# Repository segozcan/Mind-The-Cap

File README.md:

# Mind-The-Cap

This is a repository for the hardware project of the [[EE464]] Static Power Conversion II course given by [[METU]] EEE department. 
The aim of the project is to design an isolated [[DC-DC converter]], the details of which are included in the [course repository](https://github.com/odtu/ee464).

## Team Members: 

* Selin Ezgi Özcan
* Özgür Gülsuna
* Işık Emir Altunkol

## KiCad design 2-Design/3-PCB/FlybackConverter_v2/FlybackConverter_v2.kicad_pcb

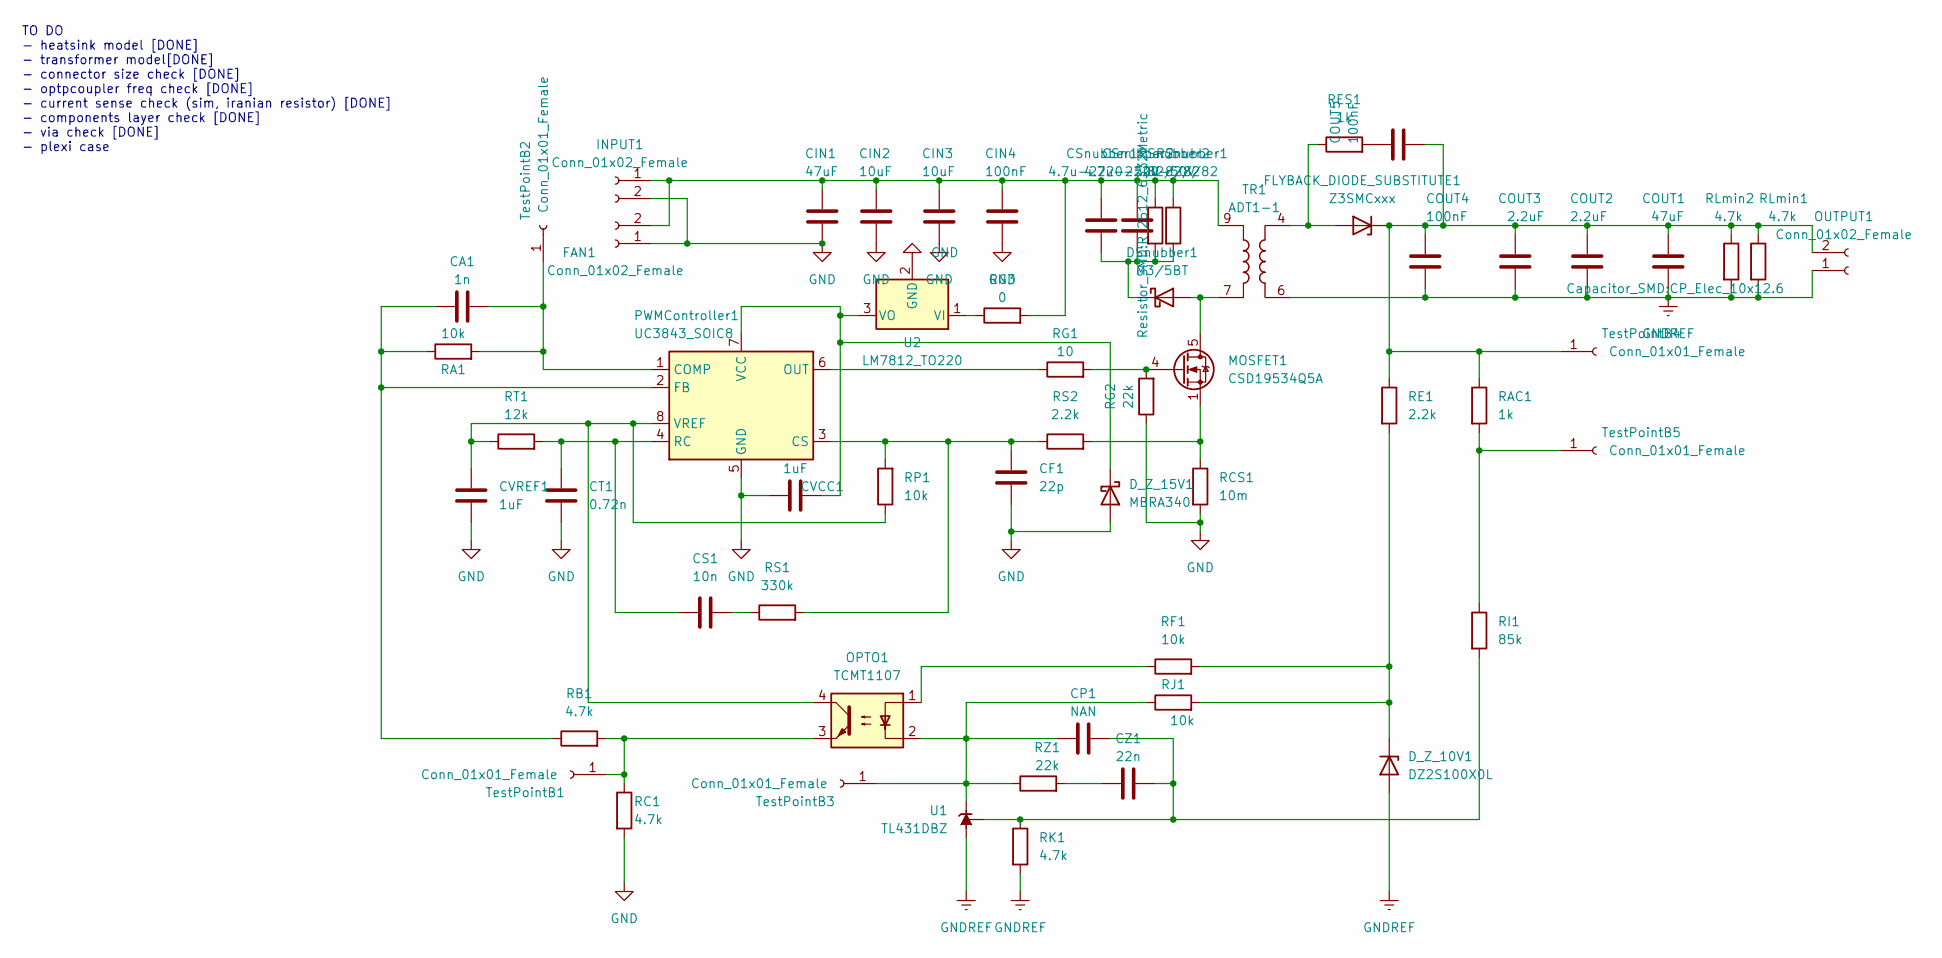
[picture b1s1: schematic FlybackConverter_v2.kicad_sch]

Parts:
CA1: 1n; C_0805_2012Metric_Pad1.18x1.45mm_HandSolder
CF1: 22p; C_0805_2012Metric_Pad1.18x1.45mm_HandSolder
CIN1: 47uF; CP_Elec_6.3x7.7
CIN2, CIN3: 10uF; C_1206_3216Metric_Pad1.33x1.80mm_HandSolder
CIN4: 100nF; C_1206_3216Metric_Pad1.33x1.80mm_HandSolder
COUT1: 47uF; CP_Elec_10x12.6
COUT2, COUT3: 2.2uF; C_1210_3225Metric_Pad1.33x2.70mm_HandSolder
COUT4: 100nF; C_1210_3225Metric_Pad1.33x2.70mm_HandSolder
COUT5: 100nF; C_1206_3216Metric
CP1: NAN; C_0805_2012Metric_Pad1.18x1.45mm_HandSolder
CS1: 10n; C_0805_2012Metric_Pad1.18x1.45mm_HandSolder
CSnubber1, CSnubber2: 4.7u-2220-50V; C_1210_3225Metric_Pad1.33x2.70mm_HandSolder
CT1: 0.72n; C_0805_2012Metric_Pad1.18x1.45mm_HandSolder
CVCC1: 1uF; C_1206_3216Metric_Pad1.33x1.80mm_HandSolder
CVREF1: 1uF; C_1206_3216Metric_Pad1.33x1.80mm_HandSolder
CZ1: 22n; C_0805_2012Metric_Pad1.18x1.45mm_HandSolder
DSnubber1: M3/5BT; D_SMB
D_Z_10V1: DZ2S100X0L; D_SOD-123
D_Z_15V1: MBRA340; D_SOD-123
FAN1: Conn_01x02_Female; PinHeader_1x02_P2.54mm_Vertical
FLYBACK_DIODE_SUBSTITUTE1: Z3SMCxxx; D_SMC
INPUT1: Conn_01x02_Female; sevgi_konnektosu
MOSFET1: CSD19534Q5A
OPTO1: TCMT1107; SOP-4_4.4x2.6mm_P1.27mm
OUTPUT1: Conn_01x02_Female; sevgi_konnektosu
PWMController1: UC3843_SOIC8; SOIC-8_3.9x4.9mm_P1.27mm
RA1: 10k; R_0805_2012Metric_Pad1.20x1.40mm_HandSolder
RAC1: 1k; R_0805_2012Metric_Pad1.20x1.40mm_HandSolder
RB1: 4.7k; R_0805_2012Metric_Pad1.20x1.40mm_HandSolder
RC1: 4.7k; R_0805_2012Metric_Pad1.20x1.40mm_HandSolder
RCS1: 10m; R_1206_3216Metric_Pad1.30x1.75mm_HandSolder
RE1: 2.2k; R_0805_2012Metric_Pad1.20x1.40mm_HandSolder
RES1: 1k; R_2512_6332Metric
RF1: 10k; R_0805_2012Metric_Pad1.20x1.40mm_HandSolder
RG1: 10; R_0805_2012Metric_Pad1.20x1.40mm_HandSolder
RG2: 22k; R_0805_2012Metric_Pad1.20x1.40mm_HandSolder
RG3: 0; R_1206_3216Metric
RI1: 85k; R_0805_2012Metric_Pad1.20x1.40mm_HandSolder
RJ1: 10k; R_0805_2012Metric_Pad1.20x1.40mm_HandSolder
RK1: 4.7k; R_0805_2012Metric_Pad1.20x1.40mm_HandSolder
RLmin1, RLmin2: 4.7k; R_1206_3216Metric_Pad1.30x1.75mm_HandSolder
RP1: 10k; R_0805_2012Metric_Pad1.20x1.40mm_HandSolder
RS1: 330k; R_0805_2012Metric_Pad1.20x1.40mm_HandSolder
RS2: 2.2k; R_0805_2012Metric_Pad1.20x1.40mm_HandSolder
RSnubber1, RSnubber2: 82//82; R_2512_6332Metric
RT1: 12k; R_0805_2012Metric_Pad1.20x1.40mm_HandSolder
RZ1: 22k; R_0805_2012Metric_Pad1.20x1.40mm_HandSolder
TR1: ADT1-1; sevgi-kafkasi
TestPointB1, TestPointB2, TestPointB3, TestPointB4, TestPointB5: Conn_01x01_Female; TestPoint_THTPad_2.0x2.0mm_Drill1.0mm
U1: TL431DBZ; SOT-23
U2: LM7812_TO220; TO-252-2

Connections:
GND: CF1.2, CIN1.2, CIN2.2, CIN3.2, CIN4.2, CT1.2, CVCC1.1, CVREF1.2, D_Z_15V1.2 (A), FAN1.1, INPUT1.2, PWMController1.5 (GND), RC1.2, RCS1.2, RG2.1, U2.2 (GND)
GNDREF: COUT1.2, COUT2.2, COUT3.2, COUT4.2, D_Z_10V1.2 (A), OUTPUT1.1, RK1.2, RLmin1.2, RLmin2.2, TR1.6, U1.3 (A)
unnamed: CA1.1, PWMController1.2 (FB), RA1.1, RB1.1
unnamed: CA1.2, PWMController1.1 (COMP), RA1.2, TestPointB2.1
unnamed: CF1.1, PWMController1.3 (CS), RP1.2, RS1.2, RS2.1
unnamed: CIN1.1, CIN2.1, CIN3.1, CIN4.1, CSnubber1.1, CSnubber2.1, FAN1.2, INPUT1.1, RG3.2, RSnubber1.1, RSnubber2.1, TR1.9
unnamed: COUT1.1, COUT2.1, COUT3.1, COUT4.1, COUT5.2, FLYBACK_DIODE_SUBSTITUTE1.1 (K), OUTPUT1.2, RAC1.1, RE1.1, RLmin1.1, RLmin2.1, TestPointB4.1
unnamed: CP1.1, OPTO1.2, RJ1.1, RZ1.1, TestPointB3.1, U1.1 (K)
unnamed: CP1.2, CZ1.2, RI1.2, RK1.1, U1.2 (REF)
unnamed: CS1.1, CT1.1, PWMController1.4 (RC), RT1.2
unnamed: CS1.2, RS1.1
unnamed: CSnubber1.2, CSnubber2.2, DSnubber1.1 (K), RSnubber1.2, RSnubber2.2
unnamed: CVCC1.2, D_Z_15V1.1 (K), PWMController1.7 (VCC), U2.3 (VO)
unnamed: CVREF1.1, OPTO1.4, PWMController1.8 (VREF), RP1.1, RT1.1
unnamed: CZ1.1, RZ1.2
unnamed: DSnubber1.2 (A), MOSFET1.5 (D), TR1.7
unnamed: D_Z_10V1.1 (K), RE1.2, RF1.2, RJ1.2
unnamed: FLYBACK_DIODE_SUBSTITUTE1.2 (A), RES1.1, TR1.4 (w~)
unnamed: MOSFET1.1 (S), RCS1.1, RS2.2
unnamed: MOSFET1.4 (G), RG1.2, RG2.2
unnamed: OPTO1.1, RF1.1
unnamed: OPTO1.3, RB1.2, RC1.1, TestPointB1.1
unnamed: PWMController1.6 (OUT), RG1.1
unnamed: RAC1.2, RI1.1, TestPointB5.1
unnamed: COUT5.1, RES1.2
unnamed: RG3.1, U2.1 (VI)

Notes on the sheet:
TO DO - heatsink model [DONE] - transformer model[DONE] - connector size check [DONE] - optpcoupler freq check [DONE] - current sense check (sim, iranian resistor) [DONE] - components layer check [DONE] - via check [DONE] - plexi case

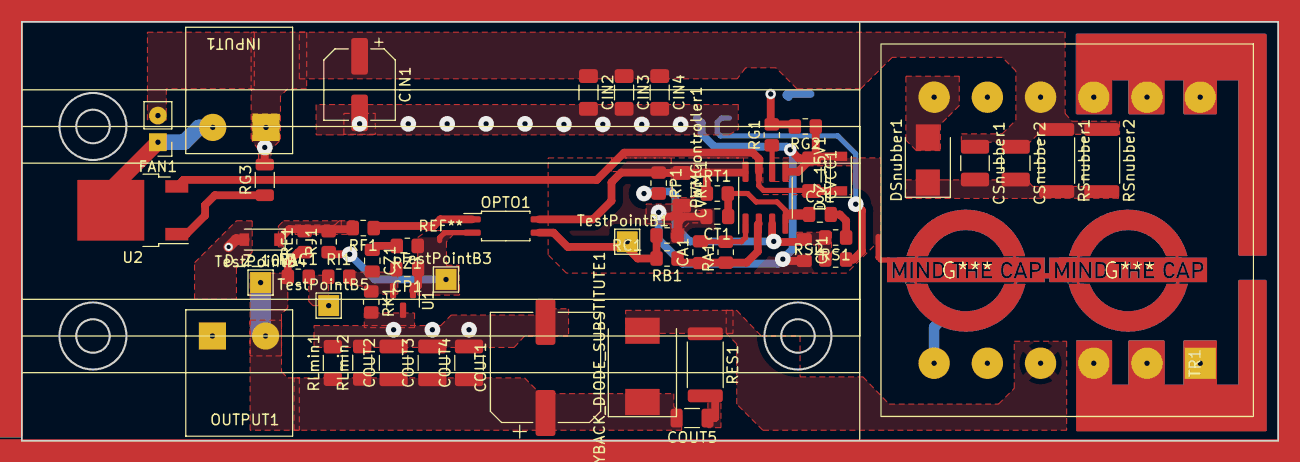
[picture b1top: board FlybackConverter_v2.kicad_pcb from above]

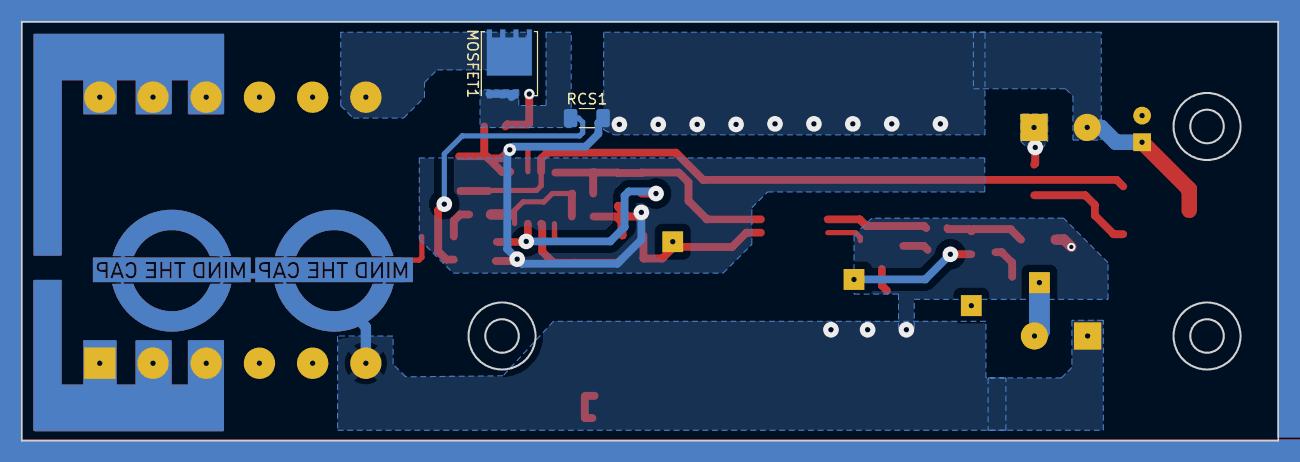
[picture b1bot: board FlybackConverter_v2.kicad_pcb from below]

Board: 2 copper layers, 119.9 x 40.0 mm, 59 parts (2 on the bottom side), 26 nets.

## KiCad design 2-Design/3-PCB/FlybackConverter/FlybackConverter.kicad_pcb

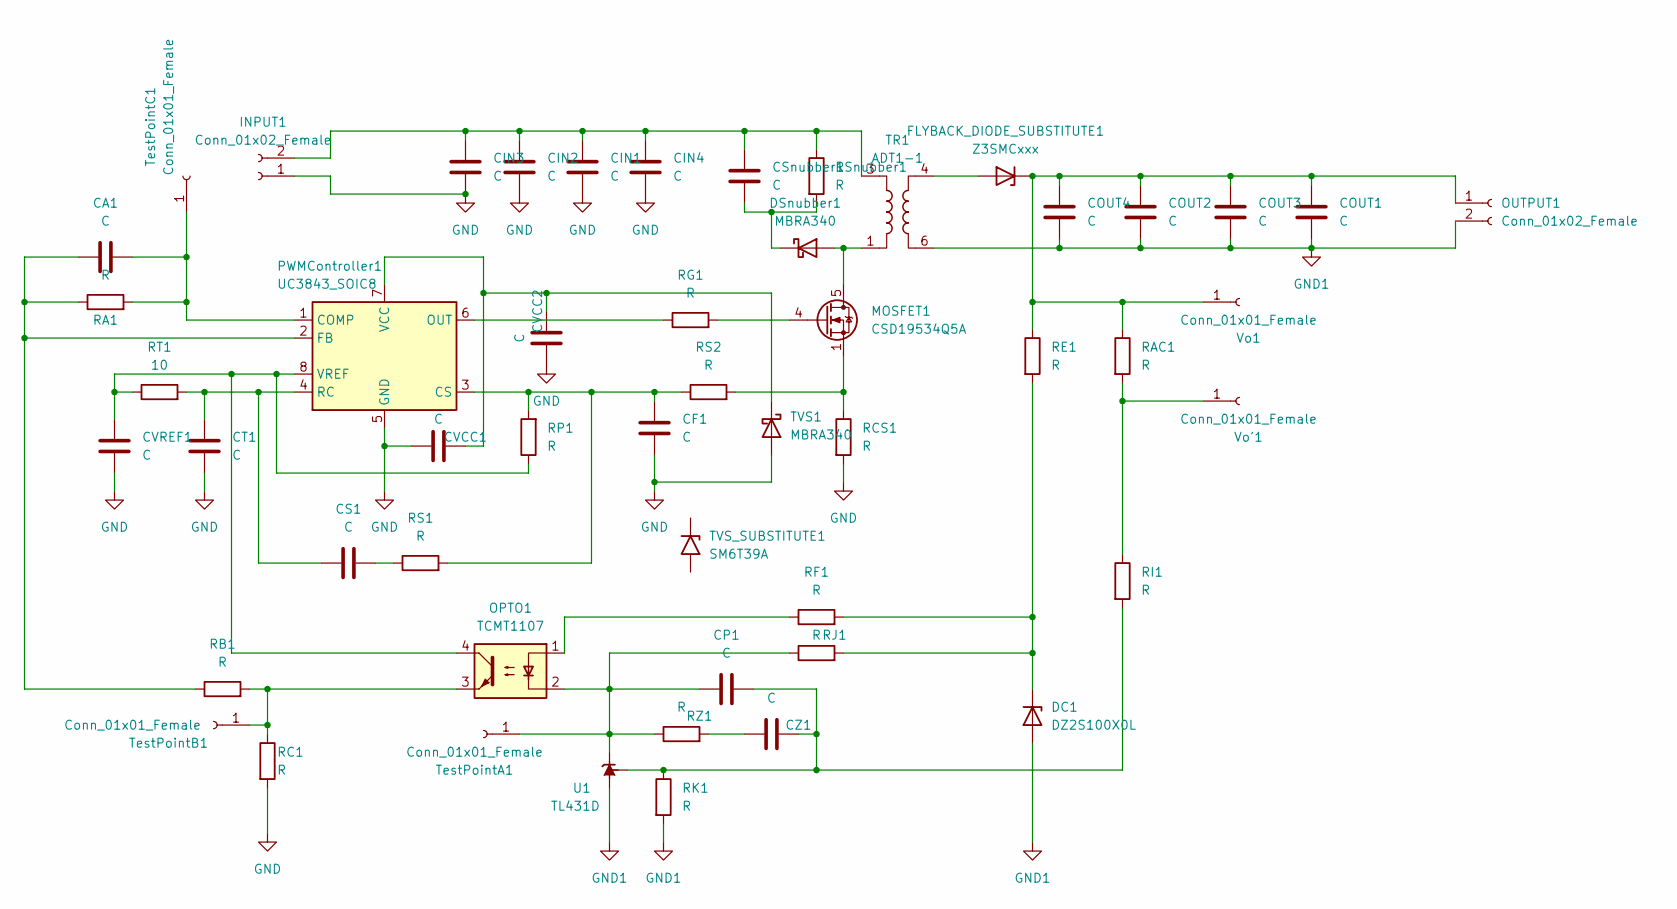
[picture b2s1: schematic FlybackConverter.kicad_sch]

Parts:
CA1: C; C_0805_2012Metric_Pad1.18x1.45mm_HandSolder
CF1: C; C_0805_2012Metric_Pad1.18x1.45mm_HandSolder
CIN1, CIN2, CIN3, CIN4: C; CP_Elec_10x10.5
COUT1, COUT2, COUT3, COUT4: C; CP_Elec_10x10.5
CP1: C; C_0805_2012Metric_Pad1.18x1.45mm_HandSolder
CS1: C; C_0805_2012Metric_Pad1.18x1.45mm_HandSolder
CSnubber1: C; C_2220_5650Metric_Pad1.97x5.40mm_HandSolder
CT1: C; C_0805_2012Metric_Pad1.18x1.45mm_HandSolder
CVCC1: C; C_0805_2012Metric_Pad1.18x1.45mm_HandSolder
CVCC2: C; CP_Elec_8x5.4
CVREF1: C; C_0805_2012Metric_Pad1.18x1.45mm_HandSolder
CZ1: C; C_0805_2012Metric_Pad1.18x1.45mm_HandSolder
DC1: DZ2S100X0L; D_SOD-523
DSnubber1: MBRA340; D_SMA
FLYBACK_DIODE_SUBSTITUTE1: Z3SMCxxx; D_SMC
INPUT1: Conn_01x02_Female; TerminalBlock_Phoenix_MKDS-1,5-2-5.08_1x02_P5.08mm_Horizont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
MOSFET1: CSD19534Q5A; TDSON-8-1
OPTO1: TCMT1107; SOP-4_4.4x2.6mm_P1.27mm
OUTPUT1: Conn_01x02_Female; TerminalBlock_Phoenix_MKDS-1,5-2-5.08_1x02_P5.08mm_Horizont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
PWMController1: UC3843_SOIC8; SOIC-8_3.9x4.9mm_P1.27mm
RA1: R; R_0805_2012Metric_Pad1.20x1.40mm_HandSolder
RAC1: R; R_0805_2012Metric_Pad1.20x1.40mm_HandSolder
RB1: R; R_0805_2012Metric_Pad1.20x1.40mm_HandSolder
RC1: R; R_0805_2012Metric_Pad1.20x1.40mm_HandSolder
RCS1: R; R_2010_5025Metric_Pad1.40x2.65mm_HandSolder
RE1: R; R_0805_2012Metric_Pad1.20x1.40mm_HandSolder
RF1: R; R_0805_2012Metric_Pad1.20x1.40mm_HandSolder
RG1: R; R_0805_2012Metric_Pad1.20x1.40mm_HandSolder
RI1: R; R_0805_2012Metric_Pad1.20x1.40mm_HandSolder
RJ1: R; R_0805_2012Metric_Pad1.20x1.40mm_HandSolder
RK1: R; R_0805_2012Metric_Pad1.20x1.40mm_HandSolder
RP1: R; R_0805_2012Metric_Pad1.20x1.40mm_HandSolder
RS1, RS2: R; R_0805_2012Metric_Pad1.20x1.40mm_HandSolder
RSnubber1: R; R_2010_5025Metric_Pad1.40x2.65mm_HandSolder
RT1: 10; R_0805_2012Metric_Pad1.20x1.40mm_HandSolder
RZ1: R; R_0805_2012Metric_Pad1.20x1.40mm_HandSolder
TR1: ADT1-1; sevgi-kafkasi
TVS1: MBRA340; D_SMA
TVS_SUBSTITUTE1: SM6T39A; D_SMB
TestPointA1: Conn_01x01_Female; TestPoint_Pad_2.5x2.5mm
TestPointB1: Conn_01x01_Female; TestPoint_Pad_2.5x2.5mm
TestPointC1: Conn_01x01_Female; TestPoint_Pad_2.5x2.5mm
U1: TL431D; SOIC-8_3.9x4.9mm_P1.27mm
Vo1: Conn_01x01_Female; TestPoint_Pad_2.5x2.5mm
Vo'1: Conn_01x01_Female; TestPoint_Pad_2.5x2.5mm

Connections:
GND: CF1.2, CIN1.2, CIN2.2, CIN3.2, CIN4.2, CT1.2, CVCC1.1, CVCC2.1, CVREF1.2, INPUT1.1, PWMController1.5 (GND), RC1.2, RCS1.2, TVS1.2 (A)
unnamed: CA1.1, PWMController1.2 (FB), RA1.1, RB1.1
unnamed: CA1.2, PWMController1.1 (COMP), RA1.2, TestPointC1.1
unnamed: CF1.1, PWMController1.3 (CS), RP1.2, RS1.2, RS2.1
unnamed: CIN1.1, CIN2.1, CIN3.1, CIN4.1, CSnubber1.1, INPUT1.2, RSnubber1.1, TR1.3
unnamed: COUT1.1, COUT2.1, COUT3.1, COUT4.1, FLYBACK_DIODE_SUBSTITUTE1.1 (K), OUTPUT1.1, RAC1.1, RE1.1, Vo1.1
unnamed: CP1.1, OPTO1.2, RJ1.1, RZ1.1, TestPointA1.1, U1.1 (K)
unnamed: CP1.2, CZ1.2, RI1.2, RK1.1, U1.8 (REF)
unnamed: CS1.1, CT1.1, PWMController1.4 (RC), RT1.2
unnamed: CS1.2, RS1.1
unnamed: CSnubber1.2, DSnubber1.1 (K), RSnubber1.2
unnamed: CVCC1.2, CVCC2.2, PWMController1.7 (VCC), TVS1.1 (K)
unnamed: CVREF1.1, OPTO1.4, PWMController1.8 (VREF), RP1.1, RT1.1
unnamed: CZ1.1, RZ1.2
unnamed: DC1.1 (K), RE1.2, RF1.2, RJ1.2
unnamed: DSnubber1.2 (A), MOSFET1.5 (D), TR1.1
unnamed: FLYBACK_DIODE_SUBSTITUTE1.2 (A), TR1.4
unnamed: MOSFET1.1 (S), MOSFET1.2 (S), MOSFET1.3 (S), RCS1.1, RS2.2
unnamed: MOSFET1.4 (G), RG1.2
unnamed: OPTO1.1, RF1.1
unnamed: OPTO1.3, RB1.2, RC1.1, TestPointB1.1
unnamed: PWMController1.6 (OUT), RG1.1
unnamed: RAC1.2, RI1.1, Vo'1.1

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
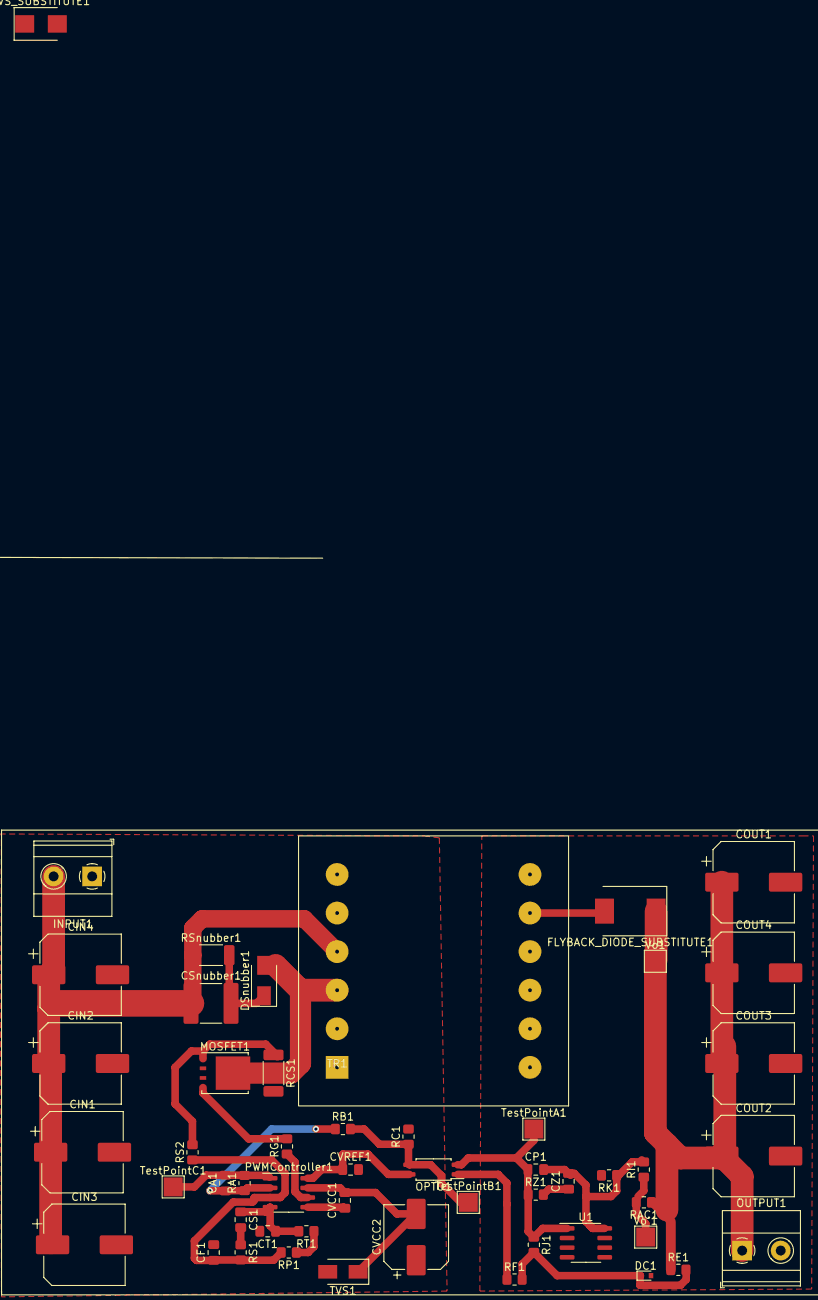
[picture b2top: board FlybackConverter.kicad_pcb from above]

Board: 2 copper layers, 52 parts (0 on the bottom side), 24 nets.

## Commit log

2023-05-01 Component List Added
2023-05-01 First flyback simulation successfully done, magnetic modelling simulation file initialized.
2023-05-01 Folder structure initialized
2023-05-03 added matlab code for magnetic design
2023-05-04 Magnetic design almost completed, measurments to be taken
2023-05-04 Magnetic design mistakes corrected, added fill factor calculations. Spice simulation consistent.
2023-05-04 Magnetic design fill factor completed for both AWG and litz.
2023-05-05 Magnetic design B_max calculated, results vary
2023-05-05 plot(B_field_2) plot(B_field)
2023-05-05 fized Npri and verified B limit
2023-05-05 added images of the report, report is at overleaf
2023-05-05 copper and core loss estimated
2023-05-05 packing factor corrected
2023-05-05 more work
2023-05-07 Magnetic design leakage inductance calculated
2023-05-07 Better estimation of copper loss
2023-05-09 Feedback Presentation
2023-05-15 [1-4] sim and report
2023-05-16 Snubber experimentations added.
2023-05-16 Snubber experimentations updated.
2023-05-24 initial schematic
2023-05-24 Added test points and connectors. No footprints yet
2023-05-26 Added footprint for the trafo
2023-05-29 i am trying to handle layout
2023-05-29 first tentavie layout
2023-06-12 something new?
2023-06-12 added vias
2023-06-14 FlybackConverter_v2 initialized, schematic and footprint updates added.
2023-06-14 FlybackConverter_v2 first placement done, gate loop is too long, positions will be updated blockwise.
2023-06-15 FlybackConverter_v2 layout updated. RJ1, 7812, and (maybe) gate driver via problematic.
2023-06-15 [sim] lt1243 as uc3843A model
2023-06-15 Small updates on schematic and layout.
2023-06-15 [model] 3d models and lib
2023-06-15 [models] rest of them
2023-06-15 Small updates & 3D models added, tracks to be placed.
2023-06-15 Tracks around the damn IC are almost done.
2023-06-15 [sim] working model
2023-06-16 Output side tracks almost completed.,
2023-06-16 I guess, only last edits left for PCB design.
2023-06-16 [sim+comp] neden acaba ?
2023-06-16 Gate loop is too long :'(. I_sense capacitor should also be placed closer to the IC.
2023-06-16 Gate loop is not long anymore. Still, why not be sad :(.
2023-06-17 [PCB] board update
2023-06-17 [PCB] snubber resistor change
2023-06-18 [PCB] last corrections and cillibom
2023-06-20 [board] last hanges
2023-06-20 [simulation] all test simulations are added
2023-06-20 [board] pdf for the print
2023-06-28 [3DModel] images and renders
2023-06-28 [control] screenshot
2023-06-28 [great-merger] - merged to main
2023-06-28 [Report] leave her Johnny, leave her
2023-08-05 [Report] more pictures
